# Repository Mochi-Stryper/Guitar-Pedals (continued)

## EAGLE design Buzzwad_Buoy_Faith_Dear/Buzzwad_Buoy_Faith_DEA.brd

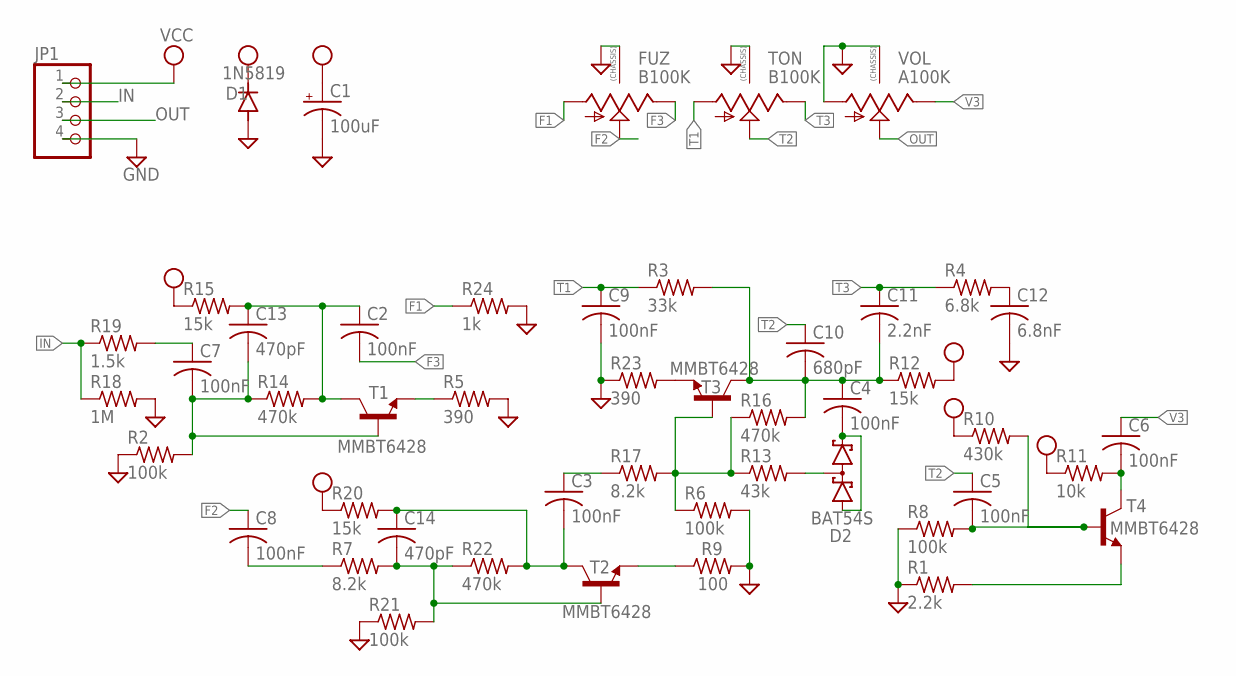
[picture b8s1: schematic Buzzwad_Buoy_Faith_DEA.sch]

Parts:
C1: 100uF; PAN_B_SMD+THRU
C2, C3, C4, C5, C6, C7, C8, C9: 100nF; C0402
C10: 680pF; C0402
C11: 2.2nF; C0402
C12: 6.8nF; C0402
C13, C14: 470pF; C0402
D1: 1N5819; SOD123
D2: BAT54S; SOT23
FUZ: B100K; 9MM_SNAP-IN_POT
JP1: PINHD-1X4; 1X04
R1: 2.2k; R0402
R2, R6, R8, R21: 100k; R0402
R3: 33k; R0402
R4: 6.8k; R0402
R5, R23: 390; R0402
R7, R17: 8.2k; R0402
R9: 100; R0402
R10: 430k; R0402
R11: 10k; R0402
R12, R15, R20: 15k; R0402
R13: 43k; R0402
R14, R16, R22: 470k; R0402
R18: 1M; R0402
R19: 1.5k; R0402
R24: 1k; R0402
T1, T2, T3, T4: MMBT6428; SOT23-BEC
TON: B100K; 9MM_SNAP-IN_POT
VOL: A100K; 9MM_SNAP-IN_POT

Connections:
F1: FUZ.1 (A), R24.1
F2: C8.1, FUZ.2 (S)
F3: C2.2, FUZ.3 (E)
GND: C1.-, C1.-- (-), C9.2, C12.2, D1.A, FUZ.CHASSIS1, FUZ.CHASSIS2, JP1.4, R1.1, R2.1, R5.2, R6.2, R8.1, R9.2, R18.2, R21.1, R23.1, R24.2, TON.CHASSIS1, TON.CHASSIS2, VOL.1 (A), VOL.CHASSIS1, VOL.CHASSIS2
IN: JP1.2, R18.1, R19.1
unnamed: C14.2, R7.2, R21.2, R22.1, T2.B
unnamed: C7.1, R19.2
unnamed: C7.2, C13.2, R2.2, R14.1, T1.B
unnamed: C2.1, C13.1, R14.2, R15.2, T1.C
unnamed: R5.1, T1.E
unnamed: C3.2, C14.1, R20.2, R22.2, T2.C
unnamed: R9.1, T2.E
unnamed: C3.1, R17.1
unnamed: R6.1, R13.1, R16.1, R17.2, T3.B
unnamed: D2.3 (C1A2), R13.2
unnamed: C4.2, D2.1 (A1), D2.2 (C2)
unnamed: R23.2, T3.E
unnamed: C4.1, C10.2, C11.2, R3.2, R12.1, R16.2, T3.C
unnamed: C12.1, R4.2
unnamed: C5.2, R8.2, R10.2, T4.B
unnamed: C6.2, R11.2, T4.C
unnamed: R1.2, T4.E
unnamed: C8.2, R7.1
OUT: JP1.3, VOL.2 (S)
T1: C9.1, R3.1, TON.1 (A)
T2: C5.1, C10.1, TON.2 (S)
T3: C11.1, R4.1, TON.3 (E)
V3: C6.1, VOL.3 (E)
VCC: C1.+, C1.++ (+), D1.C, JP1.1, R10.1, R11.1, R12.2, R15.1, R20.1

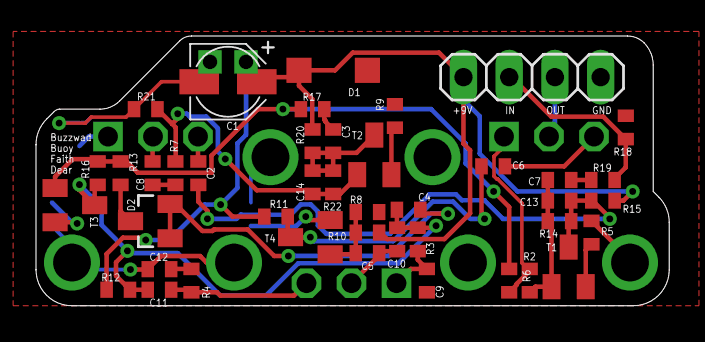
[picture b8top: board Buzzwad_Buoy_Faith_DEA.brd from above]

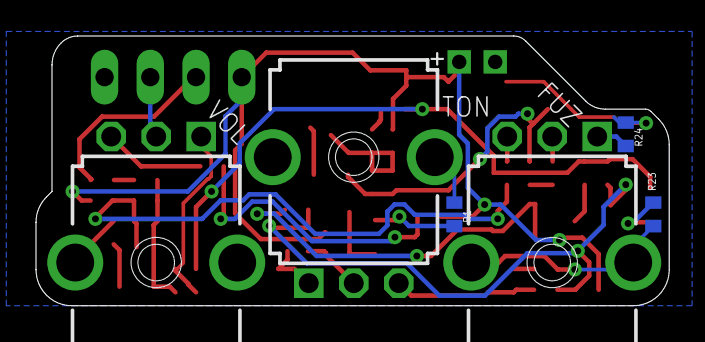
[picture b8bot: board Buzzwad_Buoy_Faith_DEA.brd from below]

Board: 2 copper layers, 35.2 x 15.0 mm, 48 parts (6 on the bottom side), 29 nets.
